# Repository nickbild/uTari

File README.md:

# µTari

µTari (pronounced micro-Tari) is an Atari 2600, only smaller. 

An original 2600 PCB measures about 9.75 x 5.25 inches. The µTari PCB is 4.7 x 3.5 inches, making it roughly one-third the size of the original. All of the original chips (6507 CPU, TIA, RIOT) were used in making the µTari — it's the real deal, not an emulator or FPGA.

<table>
  <tr>
    <td></td>
  </tr>
  <tr>
    <td align="center"><em>Original Atari 2600 PCB (top) compared with the µTari PCB (bottom).</em></td>
  </tr>
</table>

**Check out the video on YouTube:**

## How

The Atari 2600 has large switches, as well as controller and cartridge ports, that are quite nice to have for a home console. I have replaced the large switches with tiny switches and buttons. The ports have been replaced with pin headers because my eventual plan is to turn this into a handheld, so I don't want ports on the main board.

Aside from that, I removed the RF modulator (which is normally at the bottom right of the 2600 PCB) and did a composite mod that replaces it with a single transistor and two resistors. That saves a fair amount of space and produces a cleaner signal that is compatible with more modern TVs. Empty spaces on the original PCB were also cut out. 

The remainder of the circuit is copied from the original Atari PCB. The 6507, TIA, and RIOT were transplanted to the new board. Since the rest of the components (mostly resistors, capacitors, transistors, and such) can still be purchased new, I used brand-new parts to leave the original board as intact as possible. All I would need to do is pop the chips back in the IC sockets for the 2600 to work again — no Ataris were harmed in the making of the µTari.

I started by breadboarding the circuit:

Once I was convinced it was working properly, I drew the circuit diagram in KiCad before laying out a PCB and having it manufactured:

It plays just like the real thing, because it is the real thing:

## About the Author

[Nick A. Bild, MS](https://nickbild79.firebaseapp.com/#!/)

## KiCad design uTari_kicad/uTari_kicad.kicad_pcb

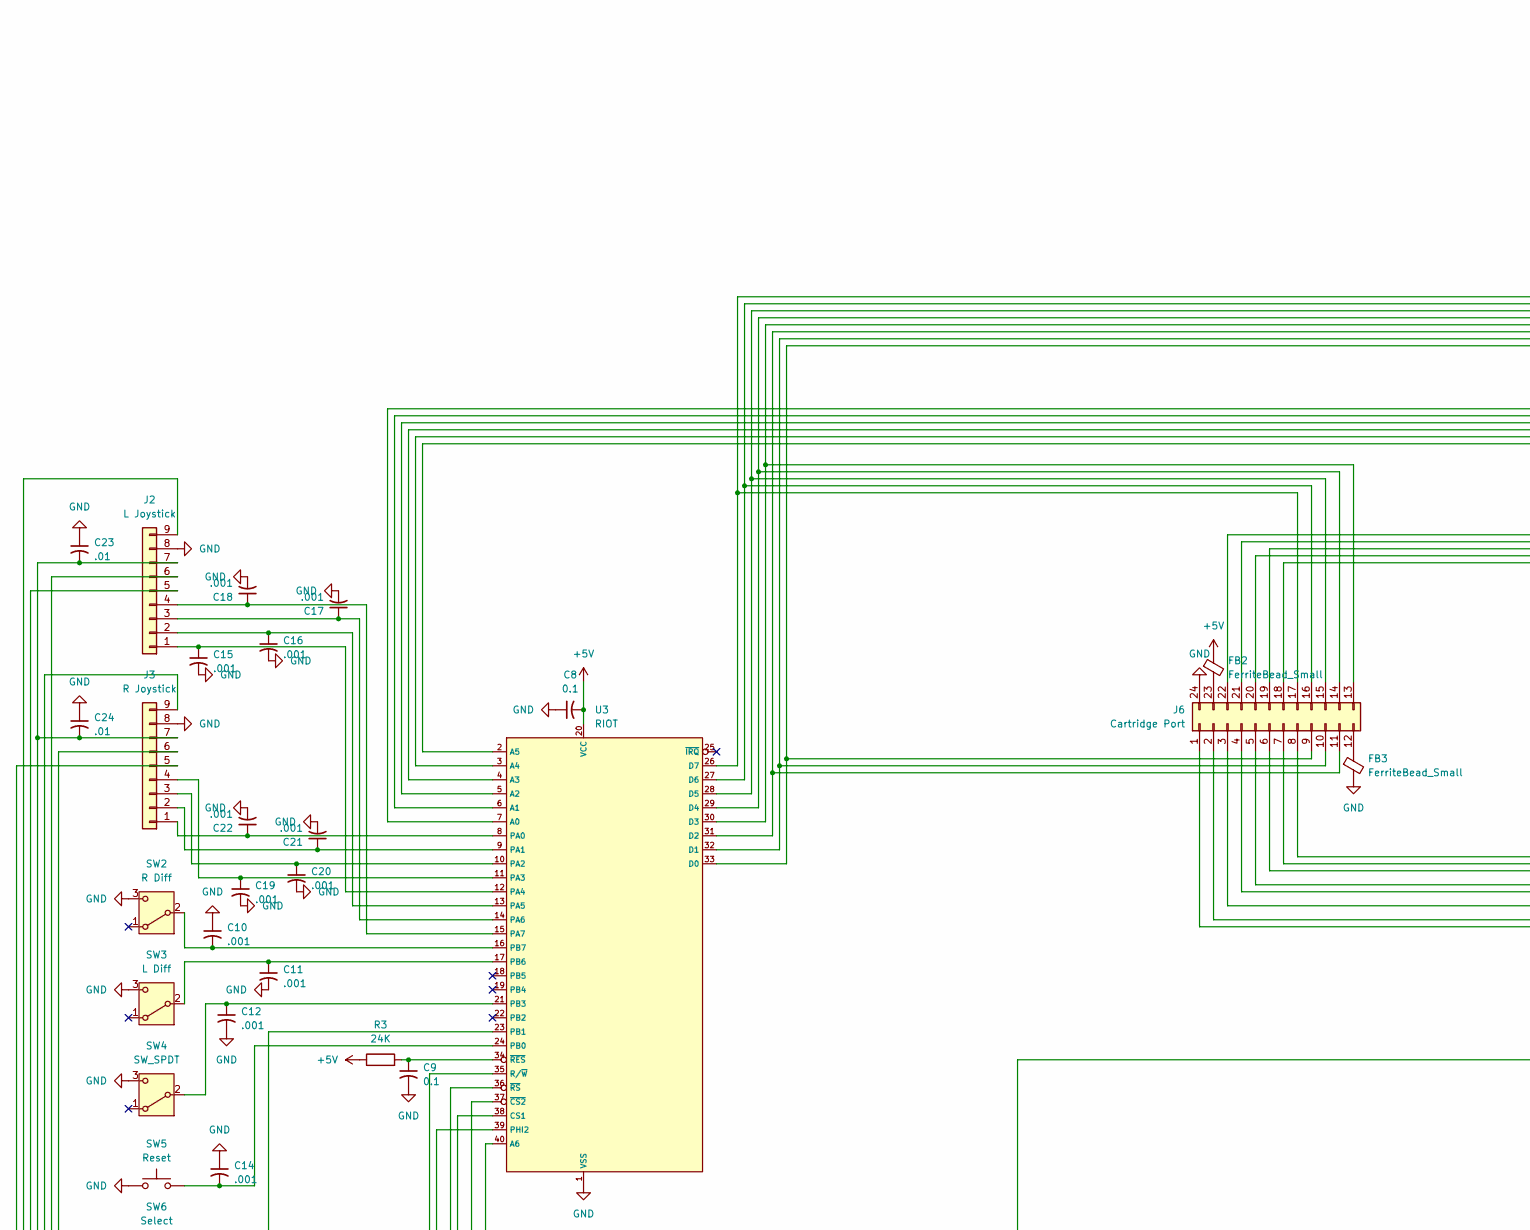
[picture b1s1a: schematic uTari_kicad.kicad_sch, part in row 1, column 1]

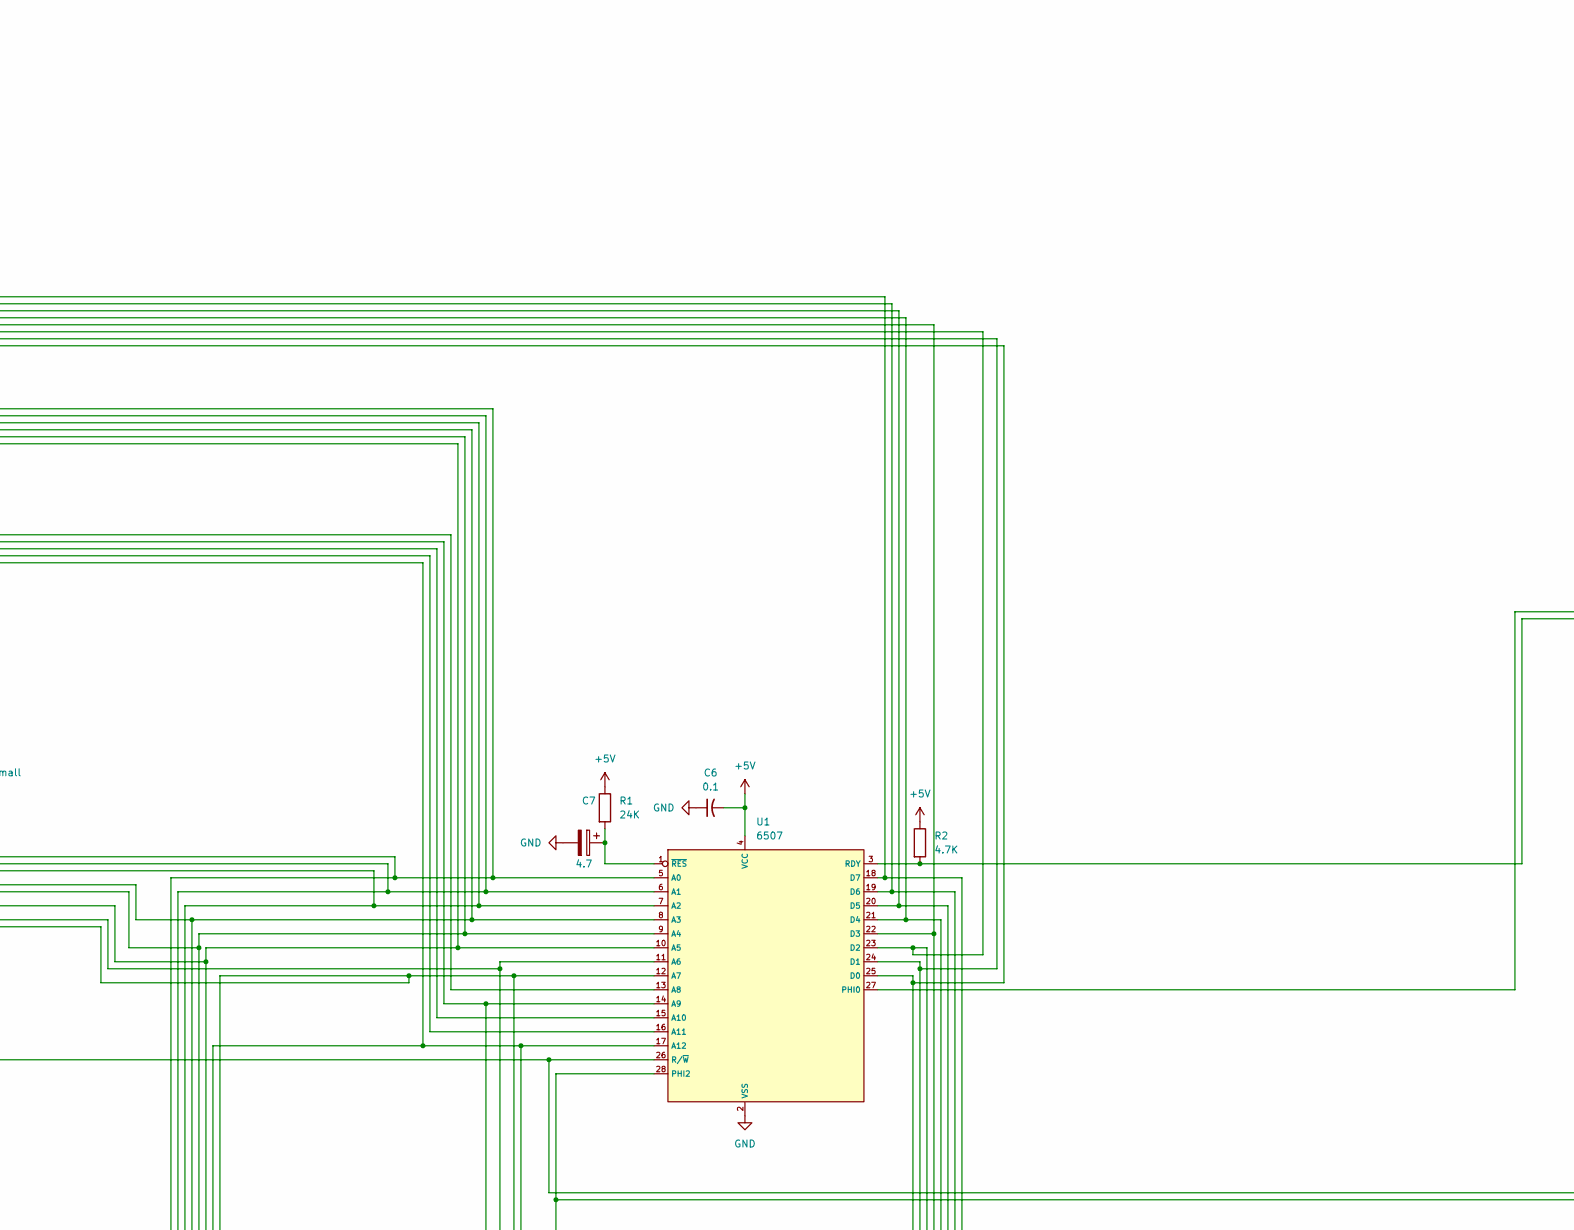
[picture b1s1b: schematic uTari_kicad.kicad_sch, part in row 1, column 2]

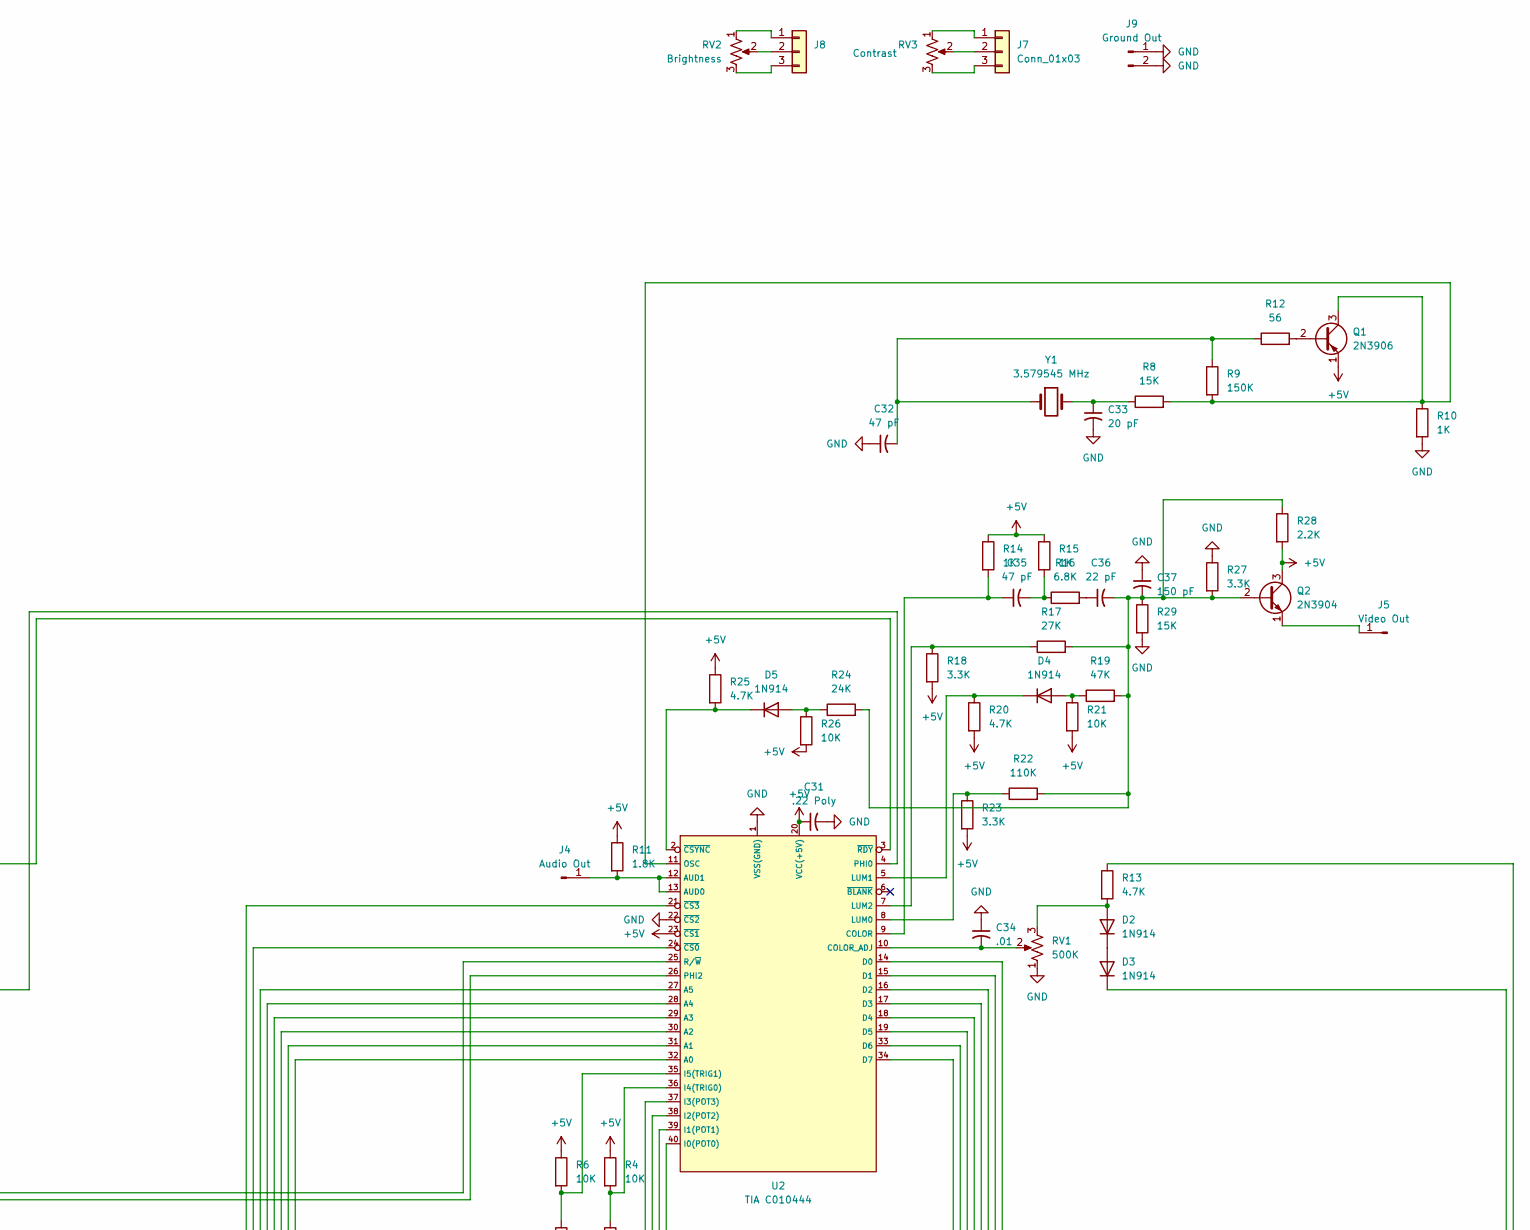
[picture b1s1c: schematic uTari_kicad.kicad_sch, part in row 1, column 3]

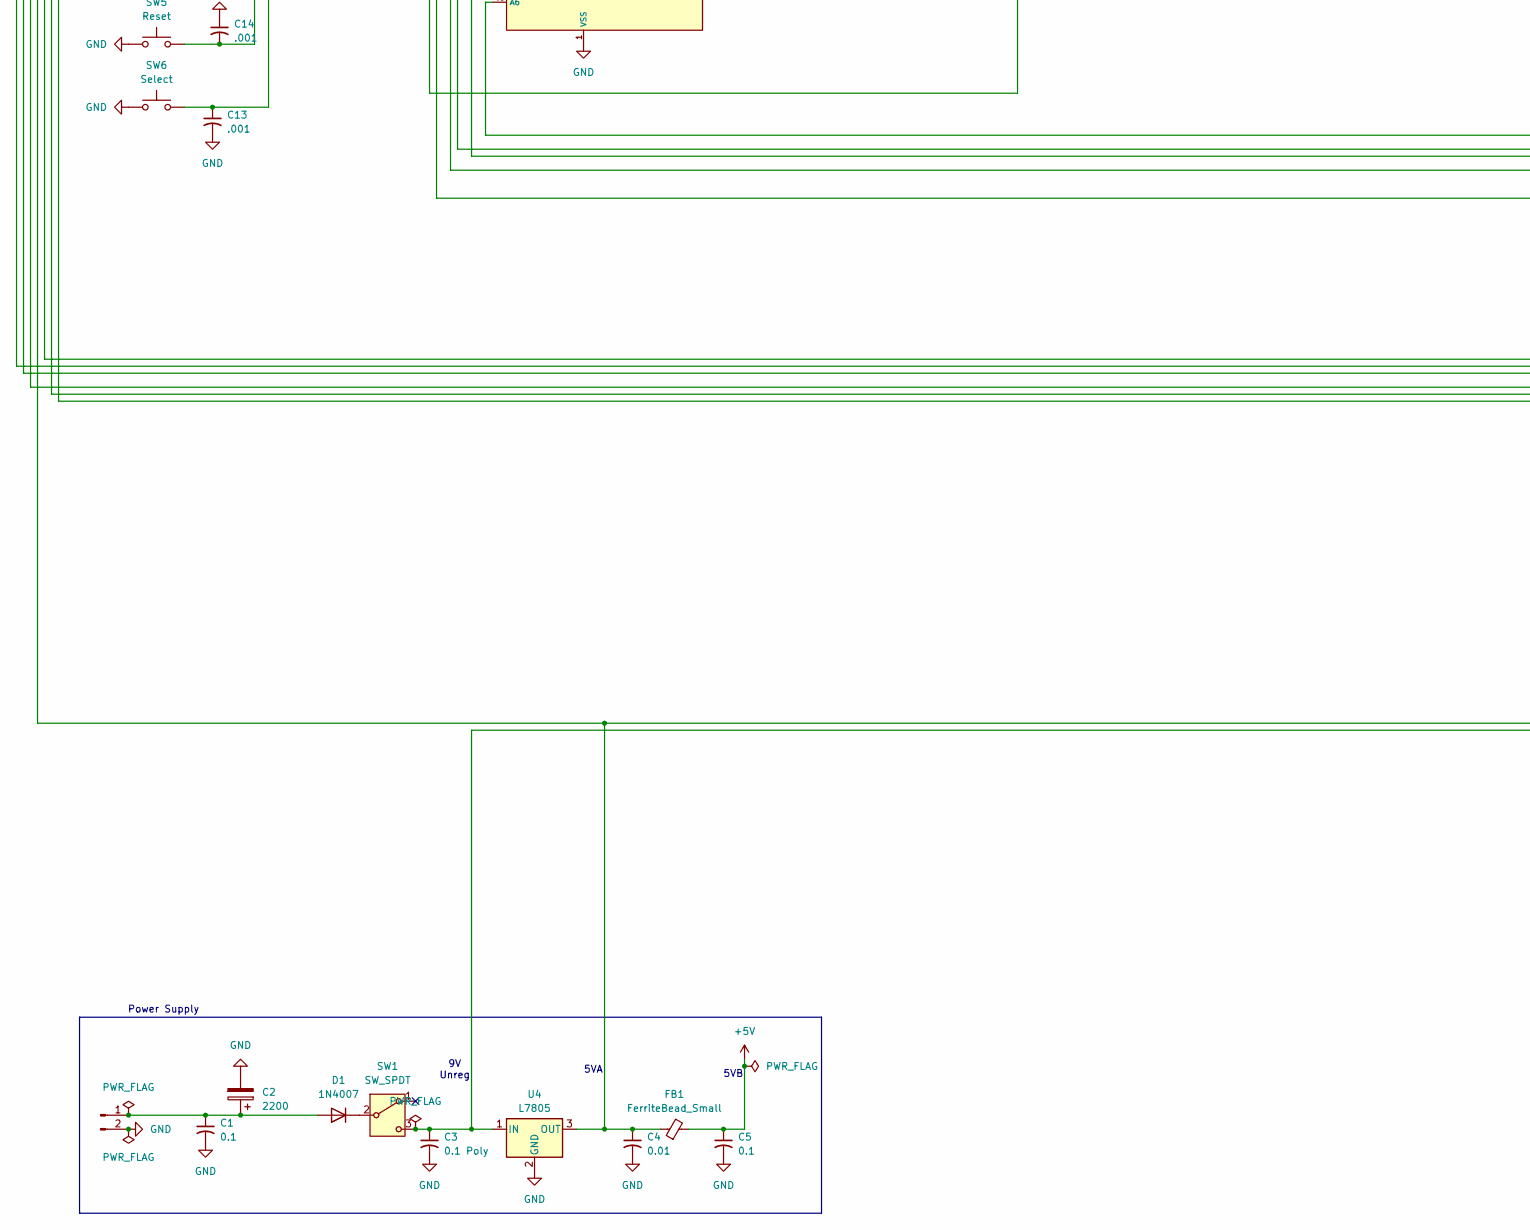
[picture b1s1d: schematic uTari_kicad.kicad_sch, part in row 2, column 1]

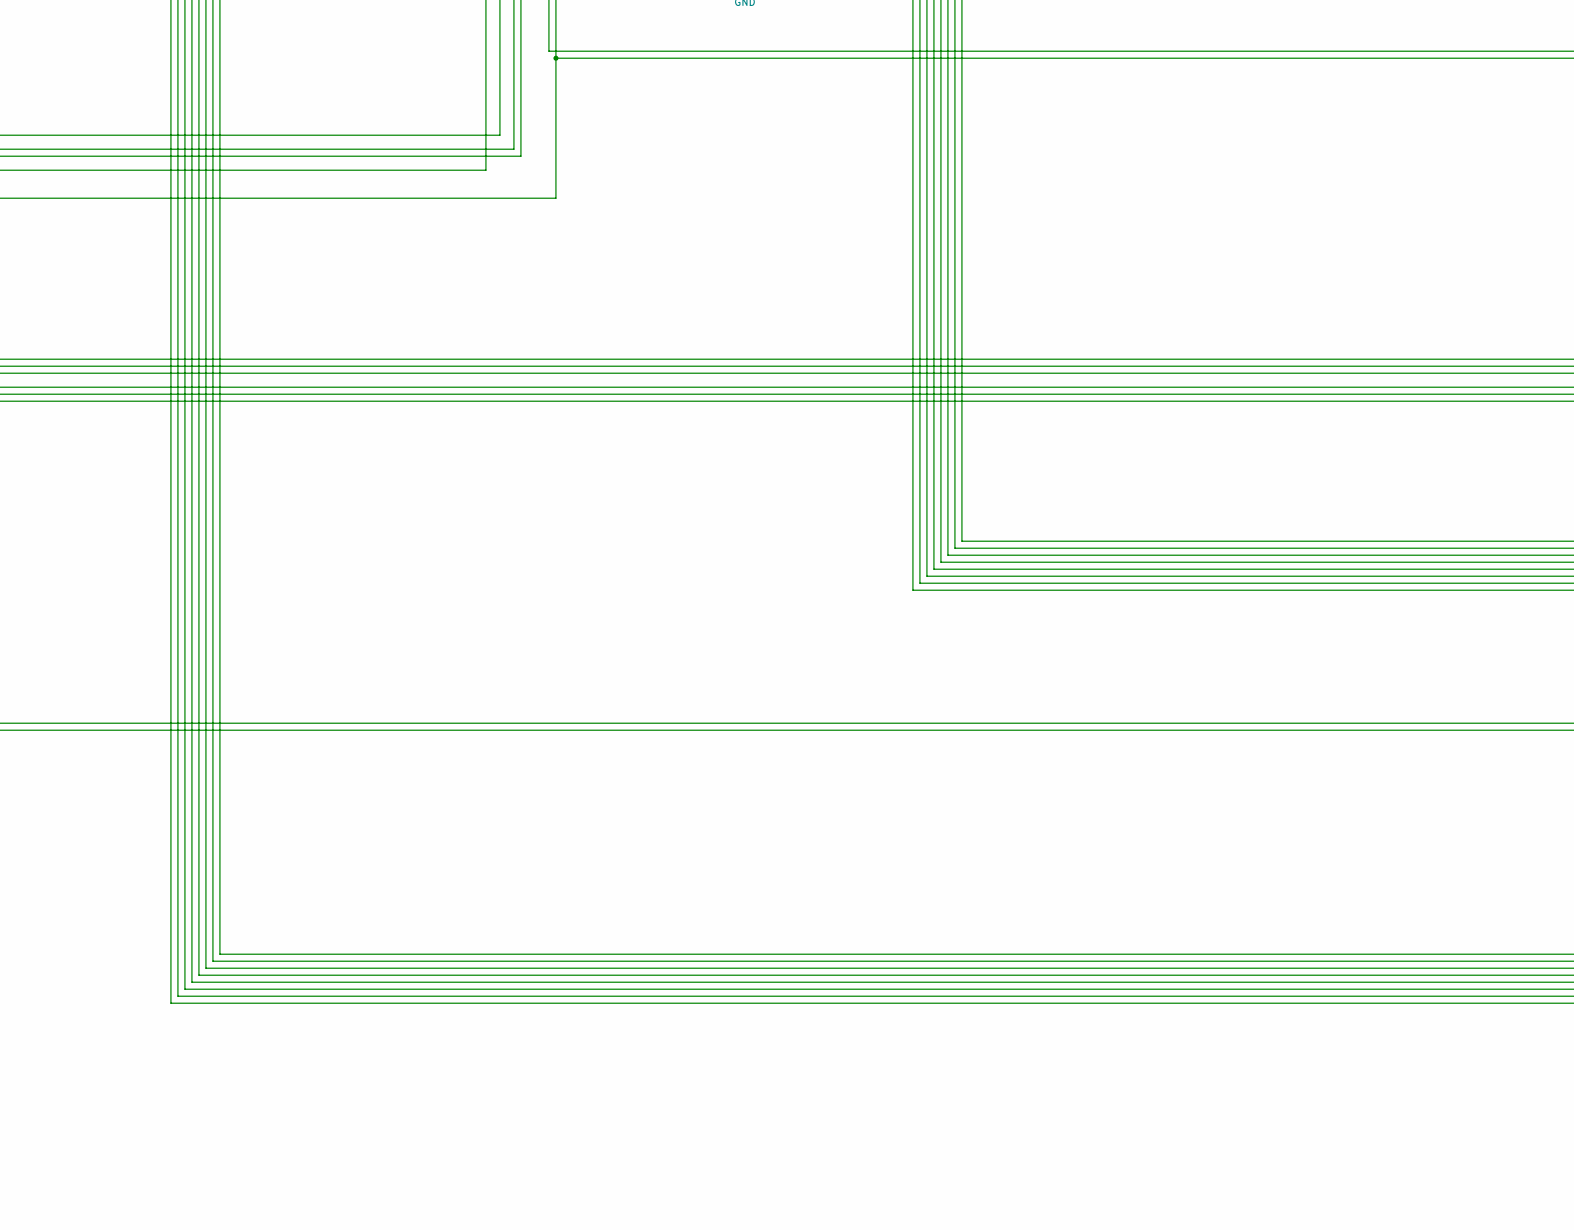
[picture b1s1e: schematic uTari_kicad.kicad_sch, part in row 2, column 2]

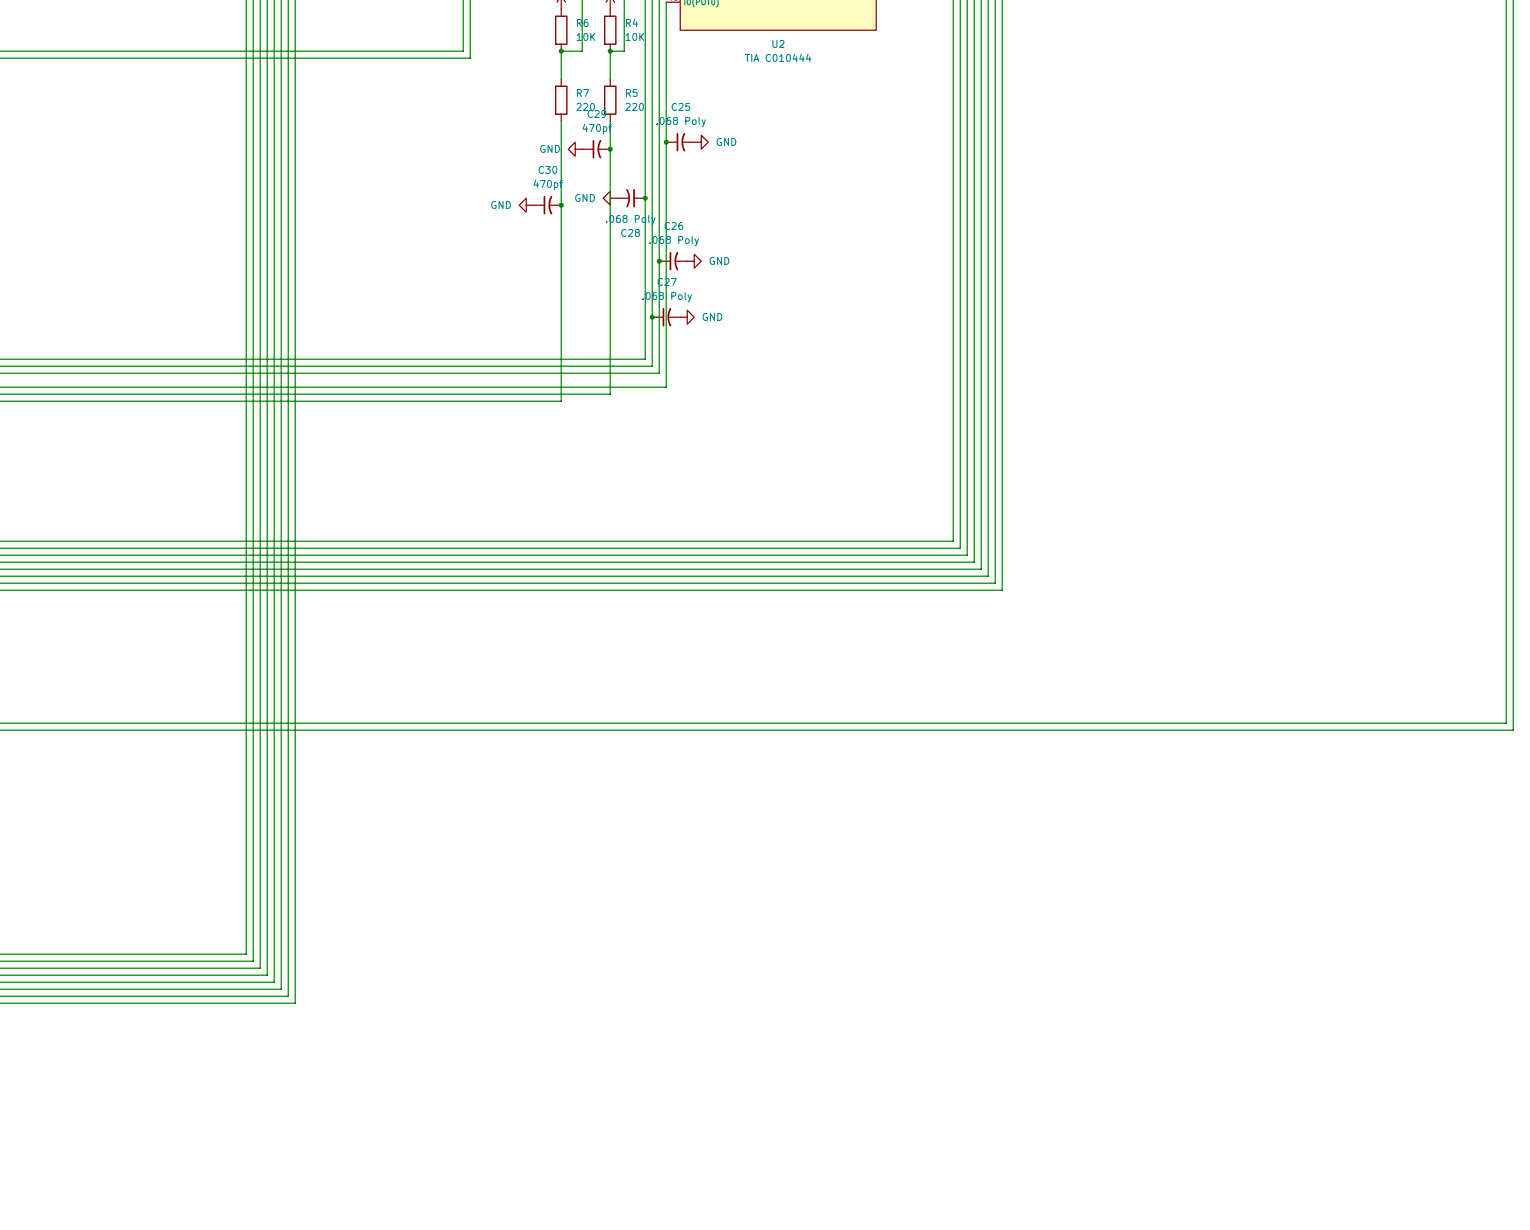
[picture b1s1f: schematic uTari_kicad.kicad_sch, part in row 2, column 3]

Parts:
C1, C5, C6, C8, C9: 0.1; C_Disc_D5.0mm_W2.5mm_P5.00mm
C2: 2200; C_Radial_D16.0mm_H31.5mm_P7.50mm
C3: 0.1 Poly; C_Disc_D11.0mm_W5.0mm_P10.00mm
C4: 0.01; C_Disc_D5.0mm_W2.5mm_P5.00mm
C7: 4.7; CP_Radial_D5.0mm_P2.50mm
C10, C11, C12, C13, C14, C15, C16, C17, C18, C19, C20, C21, C22: .001; C_Disc_D5.0mm_W2.5mm_P5.00mm
C23, C24, C34: .01; C_Disc_D5.0mm_W2.5mm_P5.00mm
C25, C26, C27, C28: .068 Poly; C_Disc_D8.0mm_W5.0mm_P7.50mm
C29, C30: 470pf; C_Disc_D5.0mm_W2.5mm_P5.00mm
C31: .22 Poly; C_Disc_D11.0mm_W5.0mm_P10.00mm
C32, C35: 47 pF; C_Disc_D5.0mm_W2.5mm_P5.00mm
C33: 20 pF; C_Disc_D5.0mm_W2.5mm_P5.00mm
C36: 22 pF; C_Disc_D5.0mm_W2.5mm_P5.00mm
C37: 150 pF; C_Disc_D5.0mm_W2.5mm_P5.00mm
D1: 1N4007; D_DO-35_SOD27_P7.62mm_Horizontal
D2, D3, D4, D5: 1N914; D_DO-35_SOD27_P7.62mm_Horizontal
FB1, FB2, FB3: FerriteBead_Small; R_Axial_DIN0207_L6.3mm_D2.5mm_P7.62mm_Horizontal
J1: Conn_01x02_Pin; PinSocket_1x02_P2.54mm_Vertical
J2: L Joystick; PinSocket_1x09_P2.54mm_Vertical
J3: R Joystick; PinSocket_1x09_P2.54mm_Vertical
J4: Audio Out; PinSocket_1x01_P2.54mm_Vertical
J5: Video Out; PinSocket_1x01_P2.54mm_Vertical
J6: Cartridge Port; PinSocket_2x12_P2.54mm_Vertical
J7, J8: Conn_01x03; PinSocket_1x03_P2.54mm_Vertical
J9: Ground Out; PinSocket_1x02_P2.54mm_Vertical
Q1: 2N3906; TO-92_Inline
Q2: 2N3904; TO-92_Inline
R1, R3, R24: 24K; R_Axial_DIN0309_L9.0mm_D3.2mm_P12.70mm_Horizontal
R2, R13, R20, R25: 4.7K; R_Axial_DIN0207_L6.3mm_D2.5mm_P7.62mm_Horizontal
R4, R6, R21, R26: 10K; R_Axial_DIN0207_L6.3mm_D2.5mm_P7.62mm_Horizontal
R5, R7: 220; R_Axial_DIN0207_L6.3mm_D2.5mm_P7.62mm_Horizontal
R8, R29: 15K; R_Axial_DIN0207_L6.3mm_D2.5mm_P7.62mm_Horizontal
R9: 150K; R_Axial_DIN0207_L6.3mm_D2.5mm_P7.62mm_Horizontal
R10, R14, R15: 1K; R_Axial_DIN0207_L6.3mm_D2.5mm_P7.62mm_Horizontal
R11: 1.8K; R_Axial_DIN0207_L6.3mm_D2.5mm_P7.62mm_Horizontal
R12: 56; R_Axial_DIN0207_L6.3mm_D2.5mm_P7.62mm_Horizontal
R16: 6.8K; R_Axial_DIN0207_L6.3mm_D2.5mm_P7.62mm_Horizontal
R17: 27K; R_Axial_DIN0207_L6.3mm_D2.5mm_P7.62mm_Horizontal
R18, R23: 3.3K; R_Axial_DIN0207_L6.3mm_D2.5mm_P7.62mm_Horizontal
R19: 47K; R_Axial_DIN0207_L6.3mm_D2.5mm_P7.62mm_Horizontal
R22: 110K; R_Axial_DIN0207_L6.3mm_D2.5mm_P7.62mm_Horizontal
R27: 3.3K; R_Axial_DIN0414_L11.9mm_D4.5mm_P15.24mm_Horizontal
R28: 2.2K; R_Axial_DIN0207_L6.3mm_D2.5mm_P7.62mm_Horizontal
RV1: 500K; Potentiometer_ACP_CA6-H2,5_Horizontal
RV2: Brightness; Potentiometer_ACP_CA6-H2,5_Horizontal
RV3: Contrast; Potentiometer_ACP_CA6-H2,5_Horizontal
SW1, SW4: SW_SPDT; PinHeader_1x03_P2.54mm_Vertical
SW2: R Diff; PinHeader_1x03_P2.54mm_Vertical
SW3: L Diff; PinHeader_1x03_P2.54mm_Vertical
SW5: Reset; SW_PUSH_6mm
SW6: Select; SW_PUSH_6mm
U1: 6507; DIP-28_W15.24mm
U2: TIA C010444; DIP-40_W15.24mm
U3: RIOT; DIP-40_W15.24mm
U4: L7805; TO-220-3_Horizontal_TabDown
Y1: 3.579545 MHz; Resonator-2Pin_W10.0mm_H5.0mm

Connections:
+5V: C5.1, C6.2, C8.2, C31.1, FB1.2, FB2.1, Q1.1 (E), Q2.3 (C), R1.1, R2.1, R3.1, R4.1, R6.1, R11.1, R14.1, R15.1, R18.2, R20.2, R21.2, R23.2, R25.1, R26.2, R28.2, U1.4 (VCC), U2.20 (VCC(+5V)), U2.23 (~CS1), U3.20 (VCC); also elsewhere on the board
GND: C1.2, C2.2, C3.2, C4.2, C5.2, C6.1, C7.2, C8.1, C9.2, C10.1, C11.2, C12.2, C13.2, C14.1, C15.2, C16.2, C17.2, C18.2, C19.2, C20.2, C21.2, C22.2, C23.1, C24.1, C25.2, C26.2, C27.2, C28.2, C29.1, C30.1, C31.2, C32.1, C33.2, C34.1, C37.1, FB3.2, J1.2, J2.8, J3.8, J6.24, J9.1, J9.2, R10.2, R27.1, R29.2, RV1.1, SW2.3 (C), SW3.3 (C), SW4.3 (C), SW5.1, SW6.1, U1.2 (VSS), U2.1 (VSS(GND)), U2.22 (~CS2), U3.1 (VSS), U4.2 (GND); also elsewhere on the board
unnamed: C32.2, R9.1, R12.1, Y1.1
unnamed: C33.1, R8.1, Y1.2
unnamed: C35.2, R15.2, R16.1
unnamed: C36.1, R16.2
unnamed: C1.1, C2.1, D1.2 (A), J1.1
unnamed: D1.1 (K), SW1.2 (B)
unnamed: D2.2 (A), R13.2, RV1.3
unnamed: D2.1 (K), D3.2 (A)
unnamed: C4.1, C23.2, C24.2, D3.1 (K), FB1.1, J2.7, J3.7, U4.3 (OUT)
unnamed: D4.2 (A), R19.1, R21.1
unnamed: D4.1 (K), R20.1, U2.5 (LUM1)
unnamed: D5.2 (A), R24.1, R26.1
unnamed: D5.1 (K), R25.2, U2.2 (~CSYNC)
unnamed: C15.1, J2.1, U3.12 (PA4)
unnamed: C16.1, J2.2, U3.13 (PA5)
unnamed: C17.1, J2.3, U3.14 (PA6)
unnamed: C18.1, J2.4, U3.15 (PA7)
unnamed: C25.1, J2.5, U2.40 (I0(POT0))
unnamed: C29.2, J2.6, R5.2
unnamed: C26.1, J2.9, U2.39 (I1(POT1))
unnamed: C22.1, J3.1, U3.8 (PA0)
unnamed: C21.1, J3.2, U3.9 (PA1)
unnamed: C20.1, J3.3, U3.10 (PA2)
unnamed: C19.1, J3.4, U3.11 (PA3)
unnamed: C27.1, J3.5, U2.38 (I2(POT2))
unnamed: C30.2, J3.6, R7.2
unnamed: C28.1, J3.9, U2.37 (I3(POT3))
unnamed: J4.1 (Pin_1_1), R11.2, U2.12 (AUD1), U2.13 (AUD0)
unnamed: J5.1 (Pin_1_1), Q2.1 (E)
unnamed: J6.1, U1.12 (A7), U2.21 (~CS3), U3.38 (CS1)
unnamed: J6.2, U1.11 (A6), U3.40 (A6)
unnamed: J6.3, U1.10 (A5), U2.27 (A5), U3.2 (A5)
unnamed: J6.4, U1.9 (A4), U2.28 (A4), U3.3 (A4)
unnamed: J6.5, U1.8 (A3), U2.29 (A3), U3.4 (A3)
unnamed: J6.6, U1.7 (A2), U2.30 (A2), U3.5 (A2)
unnamed: J6.7, U1.6 (A1), U2.31 (A1), U3.6 (A1)
unnamed: J6.8, U1.5 (A0), U2.32 (A0), U3.7 (A0)
unnamed: J6.9, U1.25 (D0), U2.14 (D0), U3.33 (D0)
unnamed: J6.10, U1.24 (D1), U2.15 (D1), U3.32 (D1)
unnamed: J6.11, U1.23 (D2), U2.16 (D2), U3.31 (D2)
unnamed: FB3.1, J6.12
unnamed: J6.13, U1.22 (D3), U2.17 (D3), U3.30 (D3)
unnamed: J6.14, U1.21 (D4), U2.18 (D4), U3.29 (D4)
unnamed: J6.15, U1.20 (D5), U2.19 (D5), U3.28 (D5)
unnamed: J6.16, U1.19 (D6), U2.33 (D6), U3.27 (D6)
unnamed: J6.17, U1.18 (D7), U2.34 (D7), U3.26 (D7)
unnamed: J6.18, U1.17 (A12), U2.24 (~CS0), U3.37 (~CS2)
unnamed: J6.19, U1.15 (A10)
unnamed: J6.20, U1.16 (A11)
unnamed: J6.21, U1.14 (A9), U3.36 (~RS)
unnamed: J6.22, U1.13 (A8)
unnamed: FB2.2, J6.23
unnamed: J7.1, RV3.1
unnamed: J7.2, RV3.2
unnamed: J7.3, RV3.3
unnamed: J8.1, RV2.1
unnamed: J8.2, RV2.2
unnamed: J8.3, RV2.3
unnamed: Q1.2 (B), R12.2
unnamed: Q1.3 (C), R8.2, R9.2, R10.1, U2.11 (OSC)
unnamed: C36.2, C37.2, Q2.2 (B), R17.2, R19.2, R22.2, R24.2, R27.2, R28.1, R29.1
unnamed: C3.1, R13.1, SW1.3 (C), U4.1 (IN)
unnamed: C10.2, SW2.2 (B), U3.16 (PB7)
unnamed: C11.1, SW3.2 (B), U3.17 (PB6)
unnamed: C12.1, SW4.2 (B), U3.21 (PB3)
unnamed: U1.27 (PHI0), U2.4 (PHI0)
unnamed: U1.28 (PHI2), U2.26 (PHI2), U3.39 (PHI2)
unnamed: R2.2, U1.3 (RDY), U2.3 (~RDY)
unnamed: U1.26 (R/~W), U2.25 (R/~W), U3.35 (R/~W)
unnamed: C7.1, R1.2, U1.1 (~RES)
unnamed: C35.1, R14.2, U2.9 (COLOR)
unnamed: C34.2, RV1.2, U2.10 (COLOR_ADJ)
unnamed: R4.2, R5.1, U2.36 (I4(TRIG0))
unnamed: R6.2, R7.1, U2.35 (I5(TRIG1))
unnamed: R22.1, R23.1, U2.8 (LUM0)
unnamed: R17.1, R18.1, U2.7 (LUM2)
unnamed: C14.2, SW5.2, U3.24 (PB0)
unnamed: C13.1, SW6.2, U3.23 (PB1)
unnamed: C9.1, R3.2, U3.34 (~RES)

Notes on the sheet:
9V Unreg
5VA
5VB
Power Supply

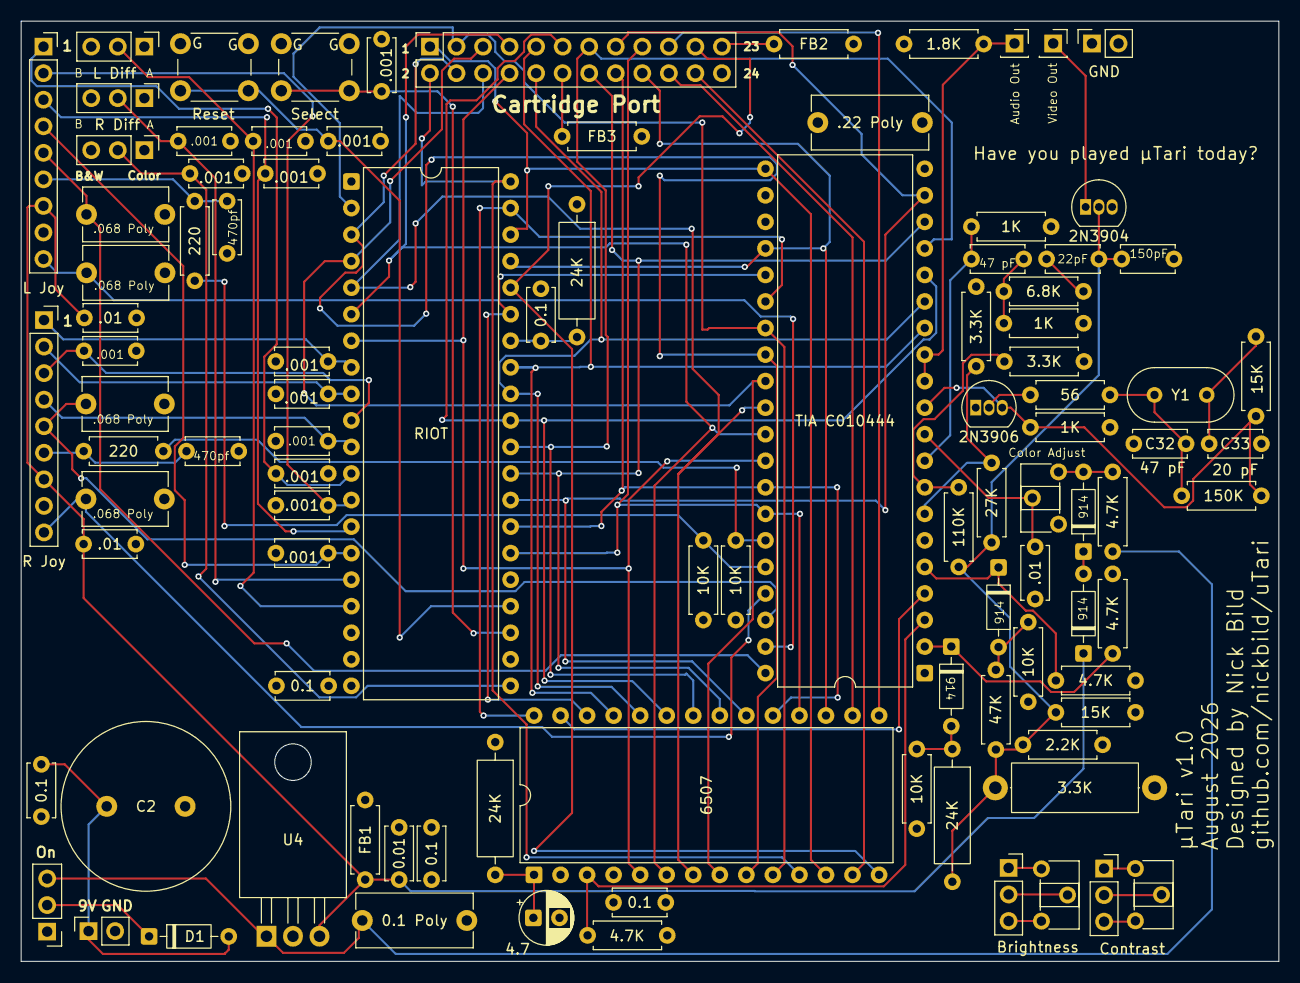
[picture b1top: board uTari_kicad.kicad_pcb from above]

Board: 4 copper layers, 120.3 x 90.0 mm, 99 parts (0 on the bottom side), 81 nets.

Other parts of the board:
0.1: 0.1; C_Disc_D5.0mm_W2.5mm_P5.00mm

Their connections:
+5V: 0.1.2; also elsewhere on the board
GND: 0.1.1; also elsewhere on the board
